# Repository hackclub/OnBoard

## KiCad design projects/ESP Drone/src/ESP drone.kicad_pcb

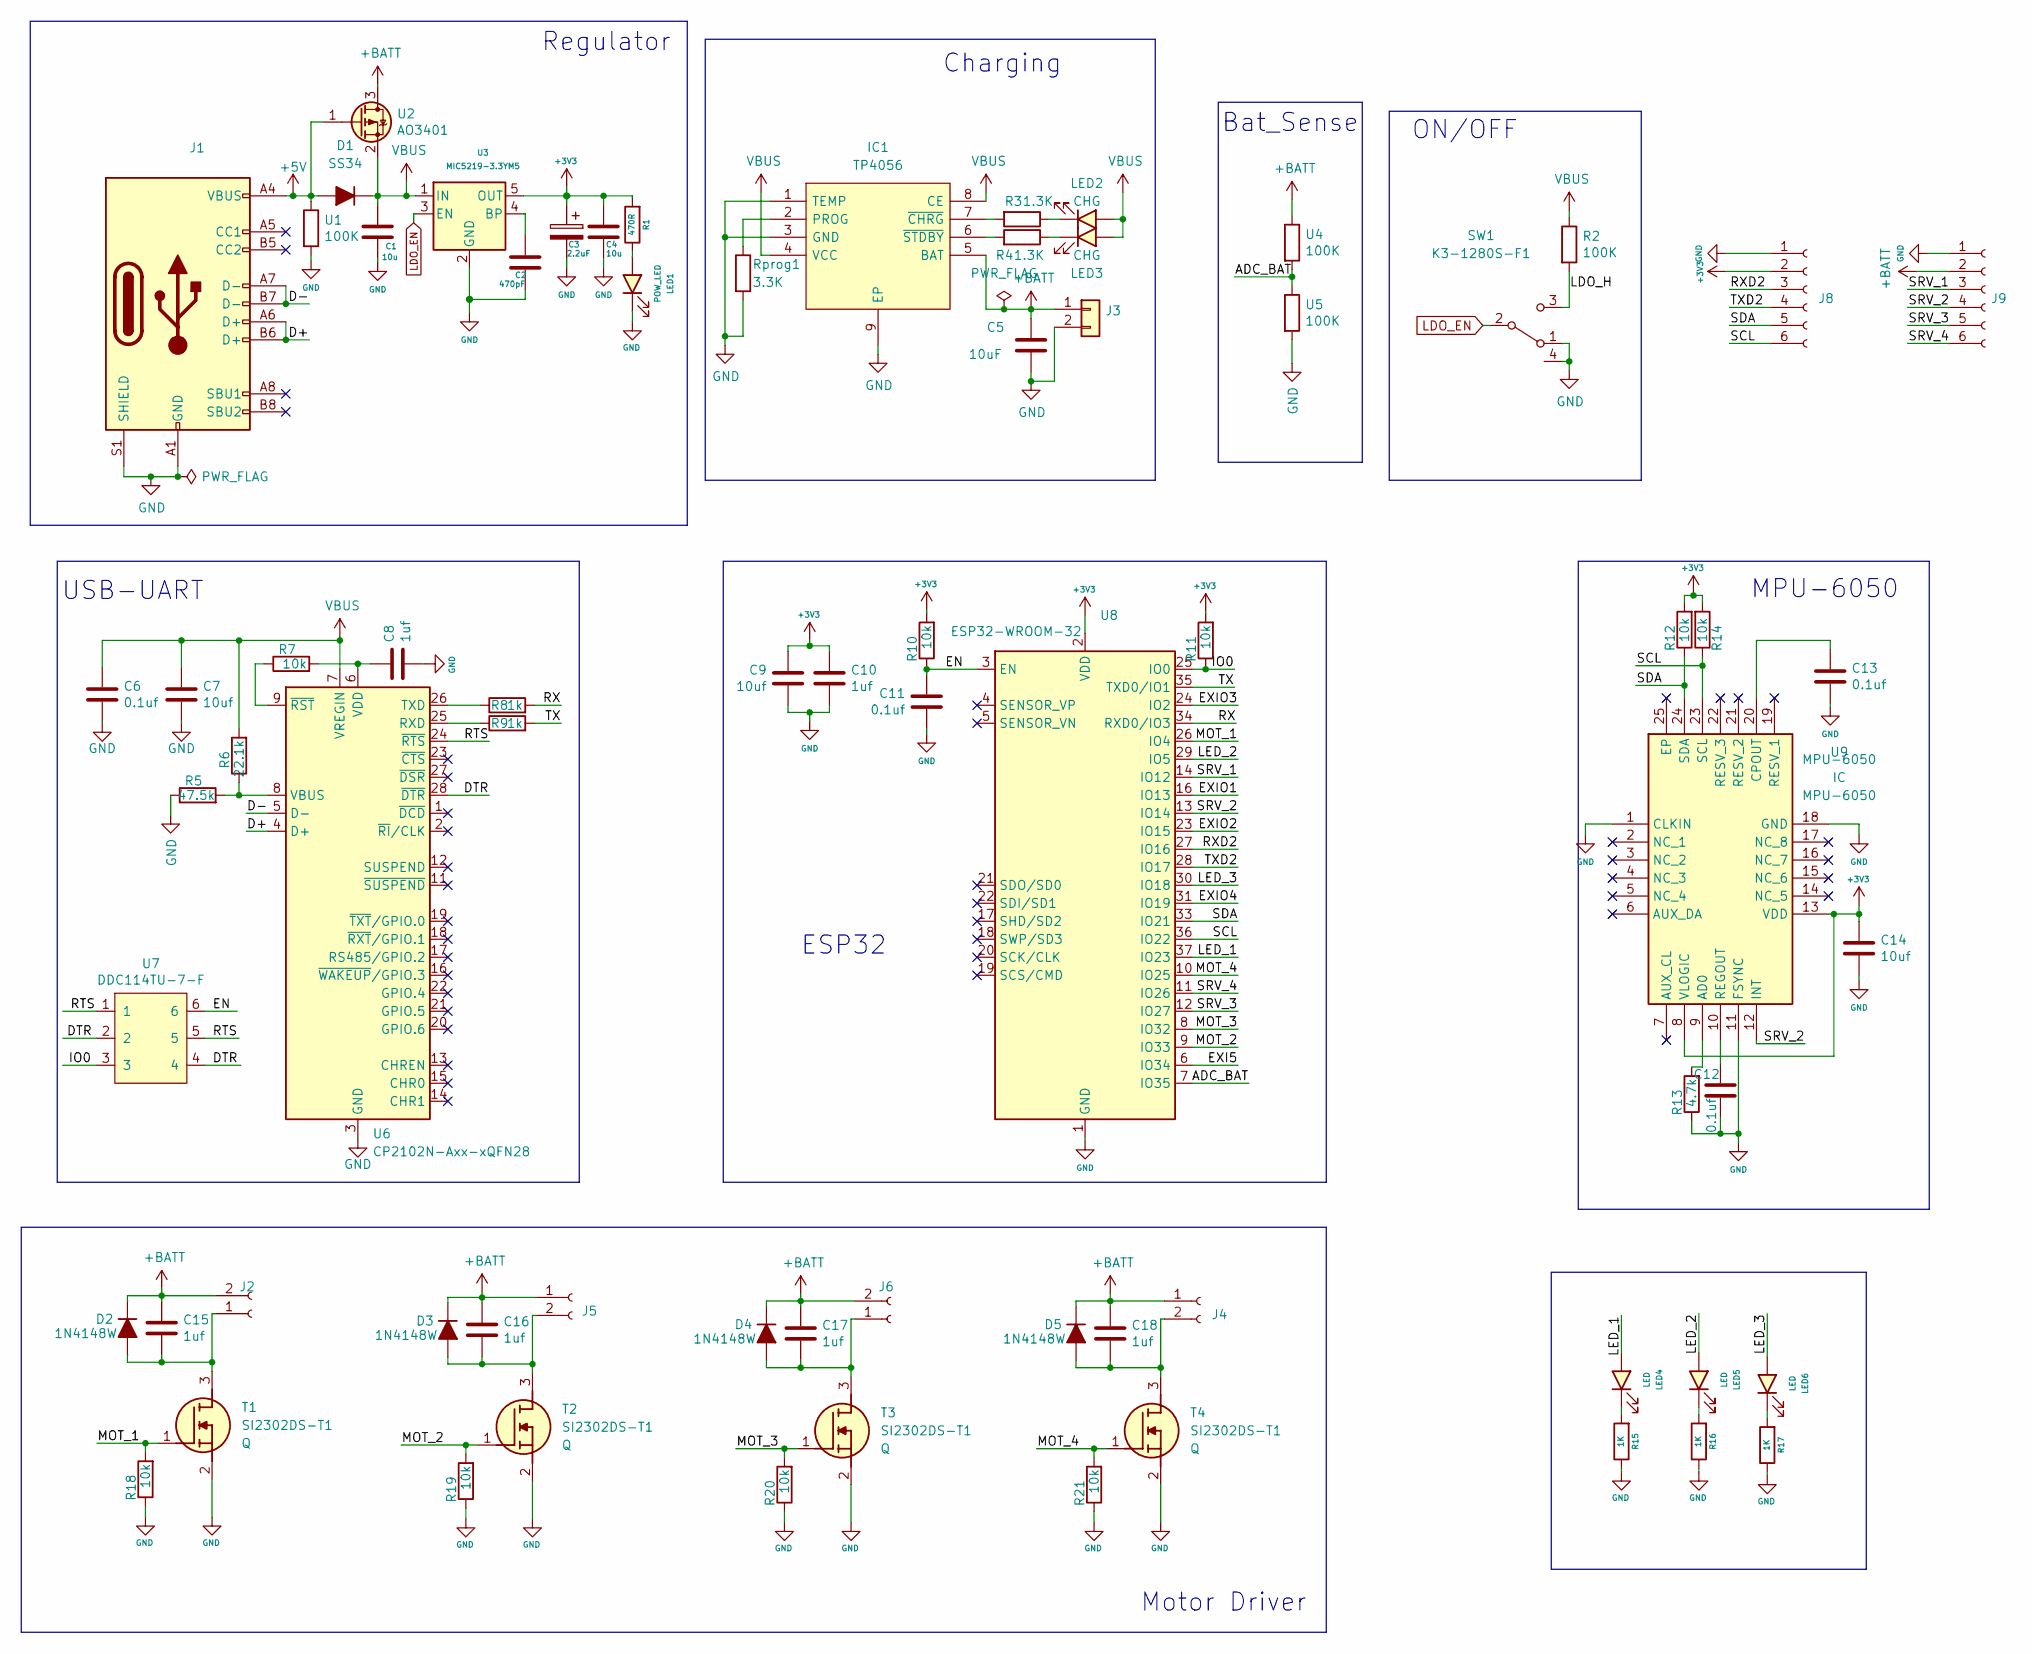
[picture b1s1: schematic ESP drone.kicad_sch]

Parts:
C1, C4: 10u; C_0603_1608Metric
C2: 470pF; C_0603_1608Metric
C3: 2.2uF; C_0805_2012Metric
C5: 10uF; C_0603_1608Metric
C6, C11, C12, C13: 0.1uf; C_0603_1608Metric
C7, C9, C14: 10uf; C_0603_1608Metric
C8, C10, C15, C16, C17, C18: 1uf; C_0603_1608Metric
D1: SS34; D_SMA
D2, D3, D4, D5: 1N4148W; D_SOD-323
IC1: TP4056; SOIC127P600X175-9N; Manufacturer_Part_Number TP4056-42-ESOP8
J1: USB_C_Receptacle_USB2.0; USB_C_Receptacle_HRO_TYPE-C-31-M-12
J2, J4, J5, J6: Conn_01x02_Female; JST_GH_SM02B-GHS-TB_1x02-1MP_P1.25mm_Horizontal
J3: B2B-PH-SM4-TB(LF)(SN); JST_PH_B2B-PH-SM4-TB_1x02-1MP_P2.00mm_Vertical
J8, J9: Conn_01x06_Female; PinHeader_1x06_P2.54mm_Vertical
LED1: POW_LED; LED_0603_1608Metric
LED2, LED3: CHG; LED_0603_1608Metric
LED4, LED5, LED6: LED; LED_0603_1608Metric
R1: 470R; R_0603_1608Metric
R2: 100K; R_0603_1608Metric
R3, R4: 1.3K; R_0603_1608Metric
R5: 47.5k; R_0603_1608Metric
R6: 22.1k; R_0603_1608Metric
R7, R10, R11, R12, R14, R18, R19, R20, R21: 10k; R_0603_1608Metric
R8, R9: 1k; R_0603_1608Metric
R13: 4.7k; R_0603_1608Metric
R15, R16, R17: 1K; R_0603_1608Metric
Rprog1: 3.3K; R_0603_1608Metric
SW1: K3-1280S-F1; slide switch spdt
T1, T2, T3, T4: SI2302DS-T1; SOT95P237X112-3N; Mouser Part Number 781-SI2302DS
U1, U4, U5: 100K; R_0603_1608Metric
U2: AO3401; SOT-23
U3: MIC5219-3.3YM5; SOT-23-5
U6: CP2102N-Axx-xQFN28; QFN-28-1EP_5x5mm_P0.5mm_EP3.35x3.35mm
U7: DDC114TU-7-F; SOT-363_SC-70-6
U8: ESP32-WROOM-32
U9: MPU-6050; MPU6050; Mouser Part Number 410-MPU-6050

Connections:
+3V3: C3.1, C4.1, C9.1, C10.1, C14.1, J8.2, R1.2, R10.2, R11.2, R12.2, R14.2, U3.5 (OUT), U8.2 (VDD), U9.8 (VLOGIC), U9.13 (VDD)
+5V: D1.2 (A), J1.A4 (VBUS), J1.A9 (VBUS), J1.B4 (VBUS), J1.B9 (VBUS), U1.1, U2.1 (G)
+BATT: C5.1, C15.1, C16.1, C17.1, C18.1, D2.1 (K), D3.1 (K), D4.1 (K), D5.1 (K), IC1.5 (BAT), J2.2, J3.1, J4.1, J5.1, J6.2, J9.2, U2.3 (D), U4.1
/ADC_BAT: U4.2, U5.1, U8.7 (IO35)
/D+: J1.A6 (D+), J1.B6 (D+), U6.4 (D+)
/D-: J1.A7 (D-), J1.B7 (D-), U6.5 (D-)
/DTR: U6.28 (~DTR), U7.2, U7.4
/EN: C11.1, R10.1, U7.6, U8.3 (EN)
/EXI5: U8.6 (IO34)
/EXIO1: U8.16 (IO13)
/EXIO2: U8.23 (IO15)
/EXIO3: U8.24 (IO2)
/EXIO4: U8.31 (IO19)
/IO0: R11.1, U7.3, U8.25 (IO0)
/LDO_H: R2.2, SW1.3 (C)
/LED_1: LED4.2 (A), U8.37 (IO23)
/LED_2: LED5.2 (A), U8.29 (IO5)
/LED_3: LED6.2 (A), U8.30 (IO18)
/MOT_1: R18.2, T1.1 (G), U8.26 (IO4)
/MOT_2: R19.2, T2.1 (G), U8.9 (IO33)
/MOT_3: R20.2, T3.1 (G), U8.8 (IO32)
/MOT_4: R21.2, T4.1 (G), U8.10 (IO25)
/RTS: U6.24 (~RTS), U7.1, U7.5
/RX: R8.2, U8.34 (RXD0/IO3)
/RXD2: J8.3, U8.27 (IO16)
/SCL: J8.6, R14.1, U8.36 (IO22), U9.23 (SCL)
/SDA: J8.5, R12.1, U8.33 (IO21), U9.24 (SDA)
/SRV_1: J9.3, U8.14 (IO12)
/SRV_2: J9.4, U8.13 (IO14), U9.12 (INT)
/SRV_3: J9.5, U8.12 (IO27)
/SRV_4: J9.6, U8.11 (IO26)
/TX: R9.2, U8.35 (TXD0/IO1)
/TXD2: J8.4, U8.28 (IO17)
GND: C1.2, C2.2, C3.2, C4.2, C5.2, C6.2, C7.2, C8.2, C9.2, C10.2, C11.2, C12.2, C13.2, C14.2, IC1.1 (TEMP), IC1.3 (GND), IC1.9 (EP), J1.A1 (GND), J1.A12 (GND), J1.B1 (GND), J1.B12 (GND), J1.S1 (SHIELD), J3.2, J8.1, J9.1, LED1.1 (K), R5.1, R13.1, R15.1, R16.1, R17.1, R18.1, R19.1, R20.1, R21.1, Rprog1.2, SW1.1 (A), SW1.4, T1.2 (S), T2.2 (S), T3.2 (S), T4.2 (S), U1.2, U3.2 (GND), U5.2, U6.3 (GND), U6.29 (GND), U8.1 (GND), U8.15 (GND), U8.38 (GND), U8.39 (GND), U9.1 (CLKIN), U9.11 (FSYNC), U9.18 (GND)
LDO_EN: SW1.2 (B), U3.3 (EN)
unnamed: C15.2, D2.2 (A), J2.1, T1.3 (D)
unnamed: C16.2, D3.2 (A), J5.2, T2.3 (D)
unnamed: C17.2, D4.2 (A), J6.1, T3.3 (D)
unnamed: C18.2, D5.2 (A), J4.2, T4.3 (D)
unnamed: IC1.2 (PROG), Rprog1.1
unnamed: IC1.7 (~CHRG), R3.2
unnamed: IC1.6 (~STDBY), R4.2
unnamed: LED1.2 (A), R1.1
unnamed: LED2.1 (K), R3.1
unnamed: LED3.1 (K), R4.1
unnamed: LED4.1 (K), R15.2
unnamed: LED5.1 (K), R16.2
unnamed: LED6.1 (K), R17.2
unnamed: C2.1, U3.4 (BP)
unnamed: R9.1, U6.25 (RXD)
unnamed: R8.1, U6.26 (TXD)
unnamed: R5.2, R6.1, U6.8 (VBUS)
unnamed: C8.1, R7.2, U6.6 (VDD)
unnamed: R7.1, U6.9 (~RST)
unnamed: R13.2, U9.9 (AD0)
unnamed: C13.1, U9.20 (CPOUT)
unnamed: C12.1, U9.10 (REGOUT)
VBUS: C1.1, C6.1, C7.1, D1.1 (K), IC1.4 (VCC), IC1.8 (CE), LED2.2 (A), LED3.2 (A), R2.1, R6.2, U2.2 (S), U3.1 (IN), U6.7 (VREGIN)

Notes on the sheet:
ESP32
ON/OFF
Bat_Sense
Motor Driver
Charging
MPU-6050
Regulator
USB-UART

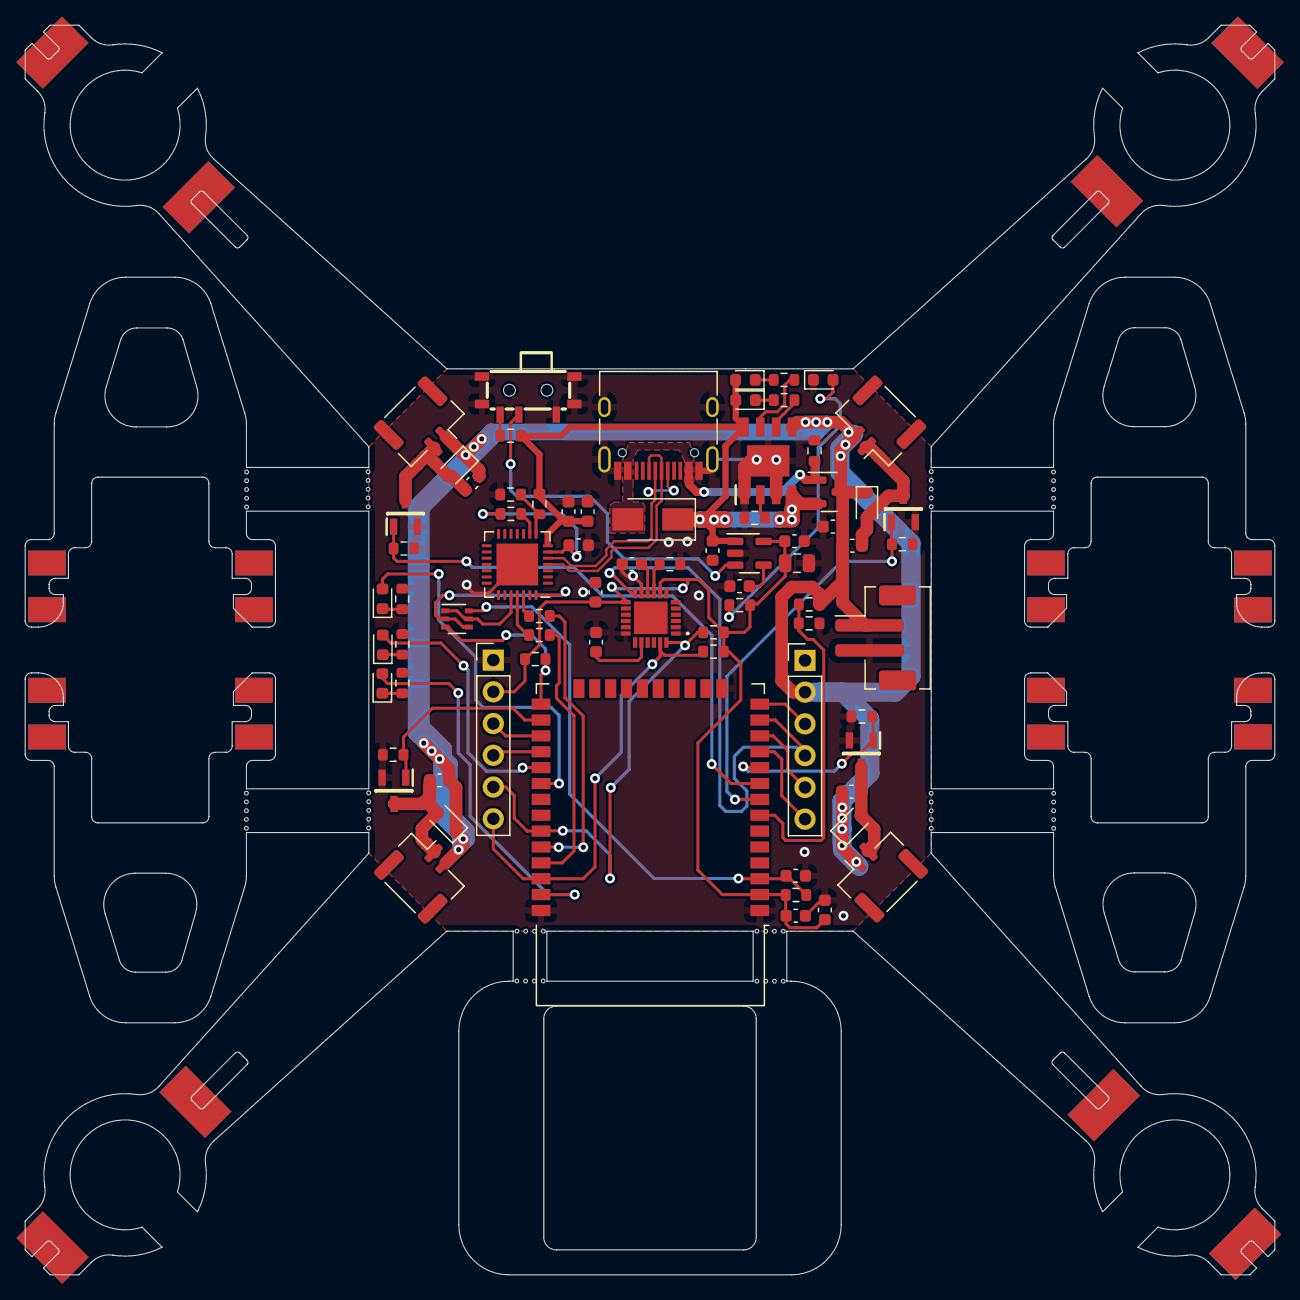
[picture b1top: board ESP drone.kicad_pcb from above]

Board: 2 copper layers, 100.0 x 100.0 mm, 74 parts (0 on the bottom side), 53 nets.

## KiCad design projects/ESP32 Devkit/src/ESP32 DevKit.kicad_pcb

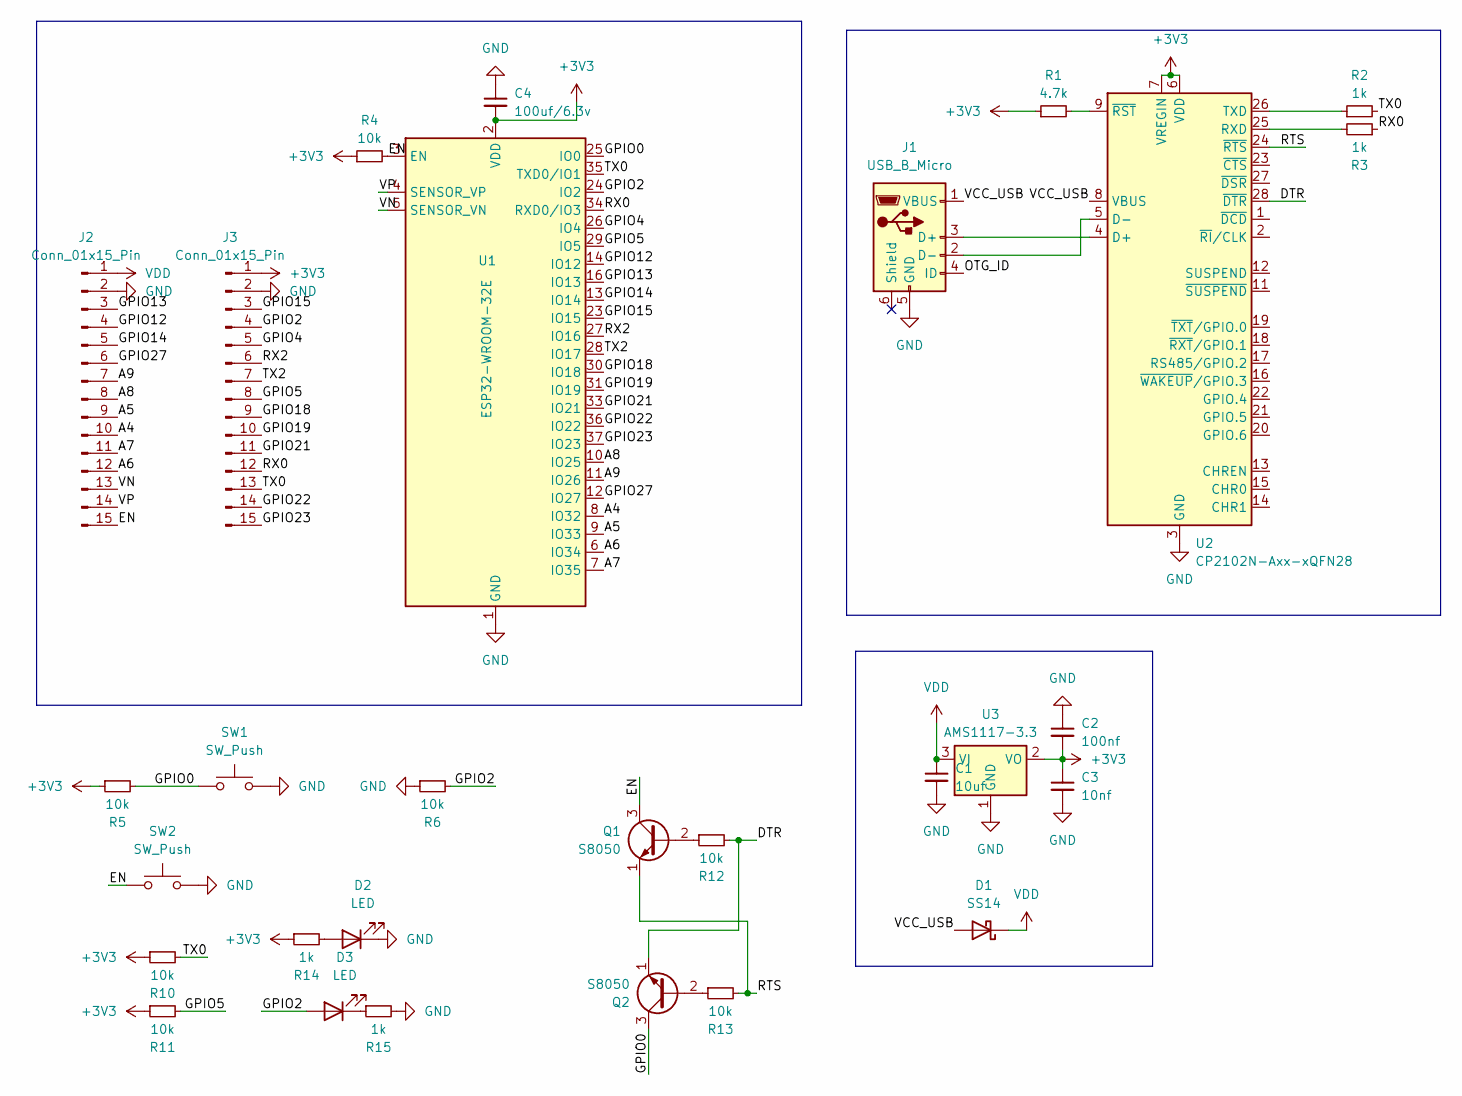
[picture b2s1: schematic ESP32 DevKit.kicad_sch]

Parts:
C1: 10uf; C_0603_1608Metric
C2: 100nf; C_0603_1608Metric
C3: 10nf; C_0603_1608Metric
C4: 100uf/6.3v; C_1206_3216Metric_Pad1.33x1.80mm_HandSolder
D1: SS14; D_SOD-123
D2, D3: LED; LED_0805_2012Metric_Pad1.15x1.40mm_HandSolder
J1: USB_B_Micro; USB_Micro-B_Amphenol_10118194-0001LF_Horizontal
J2, J3: Conn_01x15_Pin; PinHeader_1x15_P2.54mm_Vertical
Q1, Q2: S8050; TSOT-23
R1: 4.7k; R_0603_1608Metric_Pad0.98x0.95mm_HandSolder
R2, R3, R14, R15: 1k; R_0603_1608Metric_Pad0.98x0.95mm_HandSolder
R4, R5, R6, R10, R11, R12, R13: 10k; R_0603_1608Metric_Pad0.98x0.95mm_HandSolder
SW1, SW2: SW_Push; SW_Push_SPST_NO_Alps_SKRK
U1: ESP32-WROOM-32E; ESP32-WROOM-32D
U2: CP2102N-Axx-xQFN28; QFN-28-1EP_5x5mm_P0.5mm_EP3.35x3.35mm
U3: AMS1117-3.3; SOT-223-3_TabPin2

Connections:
+3V3: C2.2, C3.1, C4.2, J3.1, R1.1, R4.1, R5.1, R10.1, R11.1, R14.1, U1.2 (VDD), U2.6 (VDD), U2.7 (VREGIN), U3.2 (VO)
/A4: J2.10, U1.8 (IO32)
/A5: J2.9, U1.9 (IO33)
/A6: J2.12, U1.6 (IO34)
/A7: J2.11, U1.7 (IO35)
/A8: J2.8, U1.10 (IO25)
/A9: J2.7, U1.11 (IO26)
/DTR: Q2.1 (E), R12.2, U2.28 (~DTR)
/EN: J2.15, Q1.3 (C), R4.2, SW2.1, U1.3 (EN)
/GPIO0: Q2.3 (C), R5.2, SW1.1, U1.25 (IO0)
/GPIO2: D3.2 (A), J3.4, R6.2, U1.24 (IO2)
/GPIO4: J3.5, U1.26 (IO4)
/GPIO5: J3.8, R11.2, U1.29 (IO5)
/GPIO12: J2.4, U1.14 (IO12)
/GPIO13: J2.3, U1.16 (IO13)
/GPIO14: J2.5, U1.13 (IO14)
/GPIO15: J3.3, U1.23 (IO15)
/GPIO18: J3.9, U1.30 (IO18)
/GPIO19: J3.10, U1.31 (IO19)
/GPIO21: J3.11, U1.33 (IO21)
/GPIO22: J3.14, U1.36 (IO22)
/GPIO23: J3.15, U1.37 (IO23)
/GPIO27: J2.6, U1.12 (IO27)
/RTS: Q1.1 (E), R13.2, U2.24 (~RTS)
/RX0: J3.12, R3.1, U1.34 (RXD0/IO3)
/RX2: J3.6, U1.27 (IO16)
/TX0: J3.13, R2.2, R10.2, U1.35 (TXD0/IO1)
/TX2: J3.7, U1.28 (IO17)
/VCC_USB: D1.2 (A), J1.1 (VBUS), U2.8 (VBUS); also elsewhere on the board
/VN: J2.13, U1.5 (SENSOR_VN)
/VP: J2.14, U1.4 (SENSOR_VP)
GND: C1.2, C2.1, C3.2, C4.1, D2.1 (K), J1.5 (GND), J2.2, J3.2, R6.1, R15.2, SW1.2, SW2.2, U1.1 (GND), U1.15 (GND), U1.38 (GND), U1.39 (GND), U2.3 (GND), U2.29 (GND), U3.1 (GND); also elsewhere on the board
unnamed: D2.2 (A), R14.2
unnamed: D3.1 (K), R15.1
unnamed 34: J1.3 (D+), U2.4 (D+); also elsewhere on the board
unnamed 35: J1.2 (D-), U2.5 (D-); also elsewhere on the board
unnamed: Q1.2 (B), R12.1
unnamed: Q2.2 (B), R13.1
unnamed: R3.2, U2.25 (RXD)
unnamed: R2.1, U2.26 (TXD)
unnamed: R1.2, U2.9 (~RST)
VDD: C1.1, D1.1 (K), J2.1, U3.3 (VI)

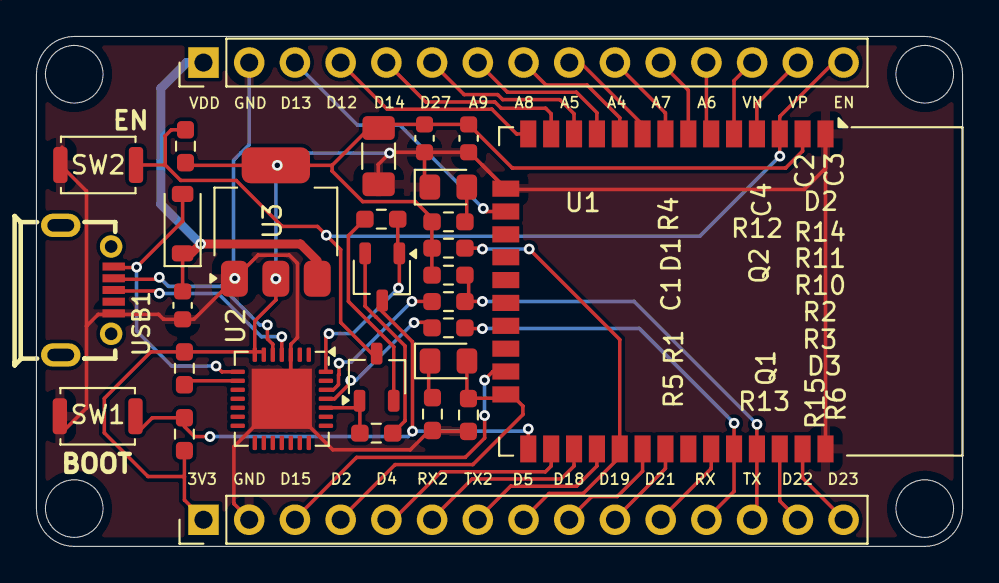
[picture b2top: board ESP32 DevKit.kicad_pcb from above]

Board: 2 copper layers, 51.5 x 28.3 mm, 29 parts (0 on the bottom side), 42 nets.

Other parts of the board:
USB1: MICRO-USB-SMD_MICRO-USB-18

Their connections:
/VCC_USB: USB1.1; also elsewhere on the board
GND: USB1.5; also elsewhere on the board
unnamed 34: USB1.3; also elsewhere on the board
unnamed 35: USB1.2; also elsewhere on the board

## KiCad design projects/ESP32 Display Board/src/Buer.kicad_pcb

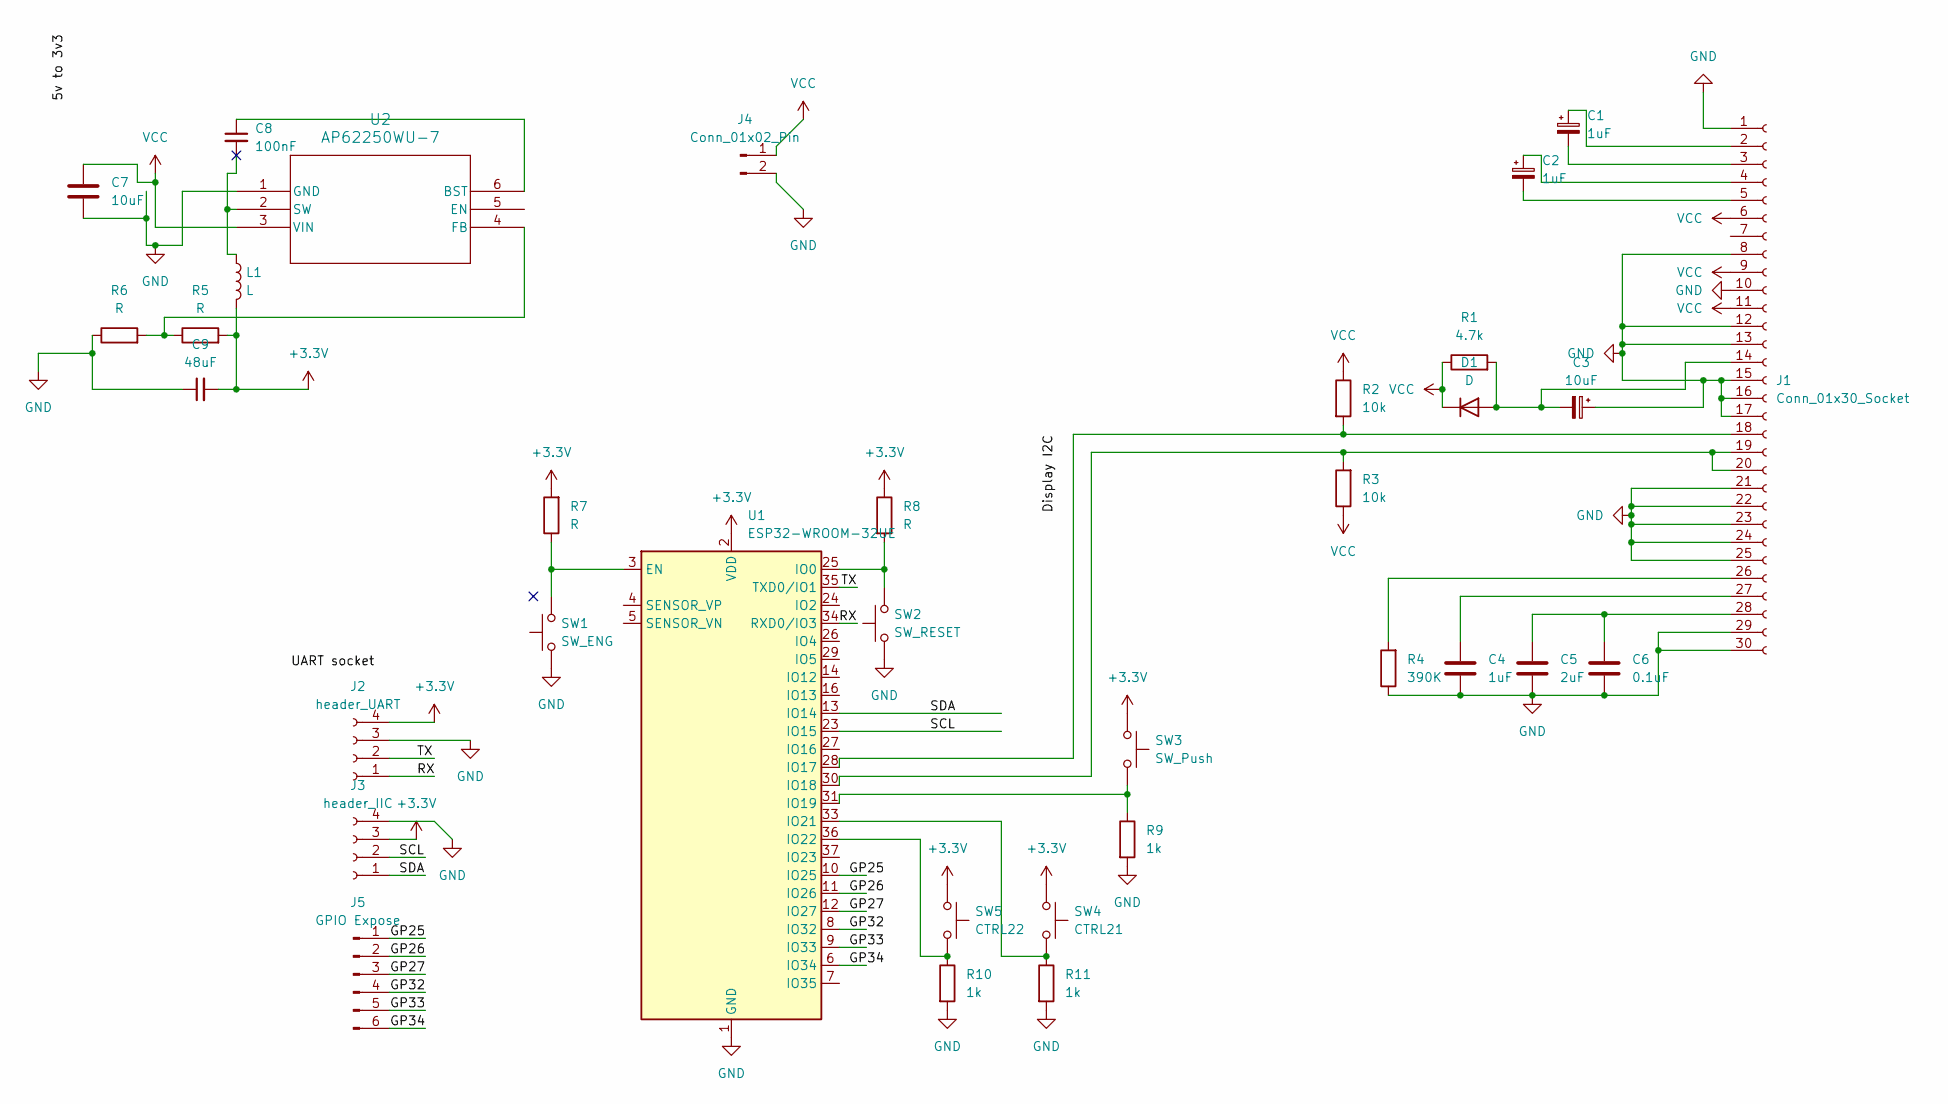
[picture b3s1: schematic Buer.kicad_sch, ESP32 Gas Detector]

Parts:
C1, C2, C4: 1uF; C_1812_4532Metric
C3, C7: 10uF; C_1812_4532Metric
C5: 2uF; C_1812_4532Metric
C6: 0.1uF; C_1206_3216Metric
C8: 100nF; C_1812_4532Metric
C9: 48uF; C_1812_4532Metric
D1: D; D_1206_3216Metric
J1: Conn_01x30_Socket; Hirose_FH12-30S-0.5SH_1x30-1MP_P0.50mm_Horizontal
J2: header_UART; JST_EH_B4B-EH-A_1x04_P2.50mm_Vertical
J3: header_IIC; NS-Tech_Grove_1x04_P2mm_Vertical
J4: Conn_01x02_Pin; TestPoint_2Pads_Pitch5.08mm_Drill1.3mm
J5: GPIO Expose; JST_PH_B6B-PH-K_1x06_P2.00mm_Vertical
L1: L; L_2010_5025Metric
R1: 4.7k; R_2512_6332Metric
R2, R3: 10k; R_2512_6332Metric
R4: 390K; R_2512_6332Metric
R5, R6, R7, R8: R; R_2512_6332Metric
R9, R10, R11: 1k; R_2512_6332Metric
SW1: SW_ENG; SW_Tactile_SPST_NO_Straight_CK_PTS636Sx25SMTRLFS
SW2: SW_RESET; SW_Tactile_SPST_NO_Straight_CK_PTS636Sx25SMTRLFS
SW3: SW_Push; SW_Tactile_SPST_NO_Straight_CK_PTS636Sx25SMTRLFS
SW4: CTRL21; SW_Tactile_SPST_NO_Straight_CK_PTS636Sx25SMTRLFS
SW5: CTRL22; SW_Tactile_SPST_NO_Straight_CK_PTS636Sx25SMTRLFS
U1: ESP32-WROOM-32UE
U2: AP62250WU-7; TSOT-23-6

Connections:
+3.3V: C9.2, J2.4, J3.3, L1.2, R5.2, R7.2, R8.1, SW3.1, SW4.1, SW5.1, U1.2 (VDD)
/GP25: J5.1, U1.10 (IO25); also elsewhere on the board
/GP26: J5.2, U1.11 (IO26); also elsewhere on the board
/GP27: J5.3, U1.12 (IO27); also elsewhere on the board
/GP32: J5.4, U1.8 (IO32); also elsewhere on the board
/GP33: J5.5, U1.9 (IO33); also elsewhere on the board
/GP34: J5.6, U1.6 (IO34); also elsewhere on the board
/RX: J2.1, U1.34 (RXD0/IO3)
/SCL: J3.2, U1.23 (IO15)
/SDA: J3.1, U1.13 (IO14)
/TX: J2.2, U1.35 (TXD0/IO1)
GND: C3.1, C4.2, C5.2, C6.2, C7.2, C9.1, J1.1, J1.8, J1.10, J1.12, J1.13, J1.15, J1.16, J1.17, J1.21, J1.22, J1.23, J1.24, J1.25, J1.29, J1.30, J2.3, J3.4, J4.2, R4.1, R6.1, R9.2, R10.2, R11.2, SW1.1, SW2.1, U1.1 (GND), U1.15 (GND), U1.38 (GND), U1.39 (GND), U2.1 (GND)
unnamed: C3.2, D1.2 (A), J1.14, R1.2
unnamed: C1.1, J1.2
unnamed: C1.2, J1.3
unnamed: C2.1, J1.4
unnamed: C2.2, J1.5
unnamed: J1.18, R2.2, U1.28 (IO17)
unnamed: J1.19, J1.20, R3.2, U1.30 (IO18)
unnamed: J1.26, R4.2
unnamed: C4.1, J1.27
unnamed: C5.1, C6.1, J1.28
unnamed: R7.1, SW1.2, U1.3 (EN)
unnamed: R8.2, SW2.2, U1.25 (IO0)
unnamed: R9.1, SW3.2, U1.31 (IO19)
unnamed: R11.1, SW4.2, U1.33 (IO21)
unnamed: R10.1, SW5.2, U1.36 (IO22)
unnamed: C8.1, U2.6 (BST)
unnamed: R5.1, R6.2, U2.4 (FB)
VCC: C7.1, D1.1 (K), J1.6, J1.9, J1.11, J4.1, R1.1, R2.1, R3.1, U2.3 (VIN)

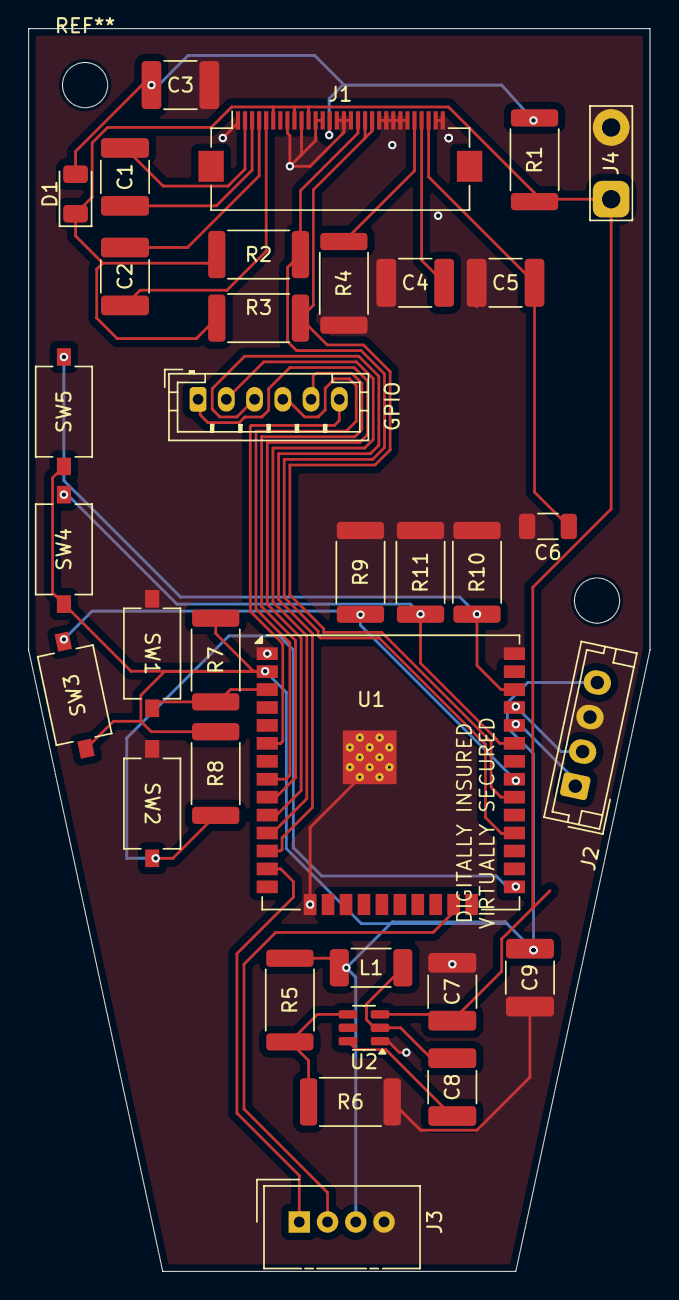
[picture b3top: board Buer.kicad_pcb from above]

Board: 2 copper layers, 44.0 x 88.0 mm, 34 parts (0 on the bottom side), 30 nets.

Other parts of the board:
GPIO: GPIO Expose; JST_PH_B6B-PH-K_1x06_P2.00mm_Vertical

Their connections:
/GP25: GPIO.1; also elsewhere on the board
/GP26: GPIO.2; also elsewhere on the board
/GP27: GPIO.3; also elsewhere on the board
/GP32: GPIO.4; also elsewhere on the board
/GP33: GPIO.5; also elsewhere on the board
/GP34: GPIO.6; also elsewhere on the board

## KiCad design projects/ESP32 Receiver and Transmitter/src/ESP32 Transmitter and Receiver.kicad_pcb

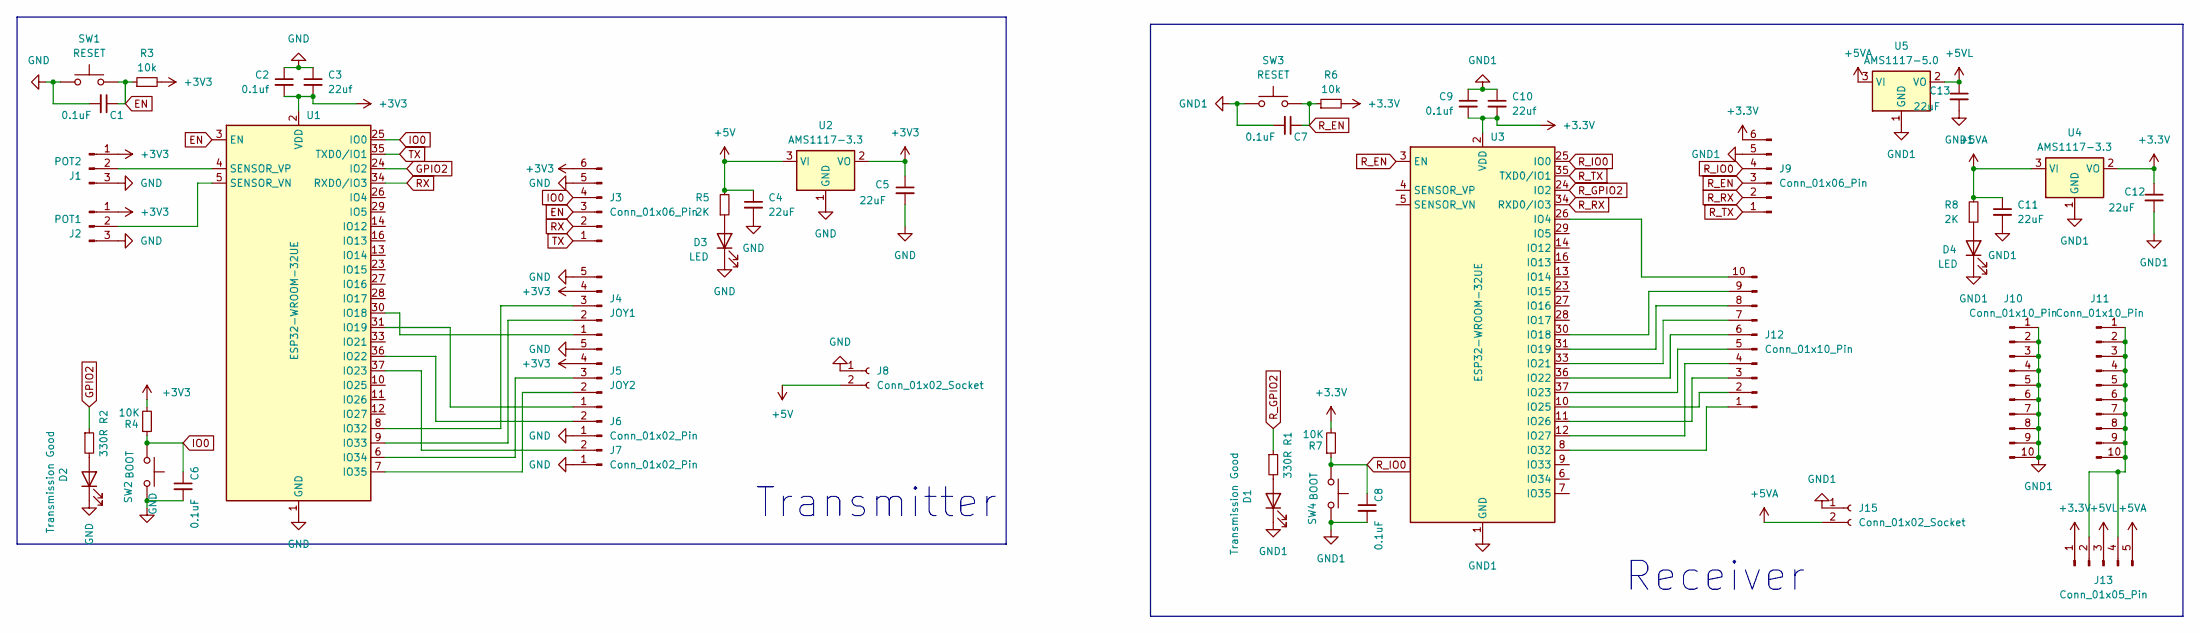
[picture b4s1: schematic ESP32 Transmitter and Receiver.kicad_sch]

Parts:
C1, C6, C7: 0.1uF; C_0805_2012Metric_Pad1.18x1.45mm_HandSolder
C2, C9: 0.1uf; C_0805_2012Metric_Pad1.18x1.45mm_HandSolder
C3, C10: 22uf; C_0805_2012Metric_Pad1.18x1.45mm_HandSolder
C4, C5, C11, C12, C13: 22uF; C_0805_2012Metric_Pad1.18x1.45mm_HandSolder
C8: 0.1uF; C_1206_3216Metric_Pad1.33x1.80mm_HandSolder
D1, D2: Transmission Good; LED_0805_2012Metric_Pad1.15x1.40mm_HandSolder
D3, D4: LED; LED_0805_2012Metric_Pad1.15x1.40mm_HandSolder
J1: POT2; PinHeader_1x03_P2.54mm_Vertical
J2: POT1; PinHeader_1x03_P2.54mm_Vertical
J3, J9: Conn_01x06_Pin; PinHeader_1x06_P2.54mm_Vertical
J4: JOY1; PinHeader_1x05_P2.54mm_Vertical
J5: JOY2; PinHeader_1x05_P2.54mm_Vertical
J6, J7: Conn_01x02_Pin; PinHeader_1x02_P2.54mm_Vertical
J8, J15: Conn_01x02_Socket; PinHeader_1x02_P2.54mm_Vertical
J10, J11, J12: Conn_01x10_Pin; PinHeader_1x10_P2.54mm_Vertical
J13: Conn_01x05_Pin; PinSocket_1x05_P2.54mm_Vertical
R1, R2: 330R; R_0805_2012Metric_Pad1.20x1.40mm_HandSolder
R3, R6: 10k; R_0805_2012Metric_Pad1.20x1.40mm_HandSolder
R4, R7: 10K; R_0805_2012Metric_Pad1.20x1.40mm_HandSolder
R5: 2K; R_0805_2012Metric_Pad1.20x1.40mm_HandSolder
R8: 2K; R_1206_3216Metric_Pad1.30x1.75mm_HandSolder
SW1, SW3: RESET; SW_Push_SPST_NO_Alps_SKRK
SW2, SW4: BOOT; SW_Push_SPST_NO_Alps_SKRK
U1, U3: ESP32-WROOM-32UE; ESP32-WROOM-32E
U2, U4: AMS1117-3.3; SOT-223-3_TabPin2
U5: AMS1117-5.0; SOT-223-3_TabPin2

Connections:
+3.3V: C9.2, C10.2, C12.1, J9.6, J13.1, R6.2, R7.2, U3.2 (VDD), U4.2 (VO)
+3V3: C2.2, C3.2, C5.1, J1.1, J2.1, J3.6, J4.4, J5.4, R3.2, R4.2, U1.2 (VDD), U2.2 (VO)
+5V: C4.1, J8.2, R5.2, U2.3 (VI)
+5VA: C11.1, J13.5, J15.2, R8.2, U4.3 (VI), U5.3 (VI)
+5VL: C13.1, J13.3, U5.2 (VO)
EN: C1.1, J3.3, R3.1, SW1.2, U1.3 (EN)
GND: C1.2, C2.1, C3.1, C4.2, C5.2, C6.2, D2.1 (K), D3.1 (K), J1.3, J2.3, J3.5, J4.5, J5.5, J6.1, J7.1, J8.1, SW1.1, SW2.2, U1.1 (GND), U1.15 (GND), U1.38 (GND), U1.39 (GND), U2.1 (GND)
GND1: C7.2, C8.2, C9.1, C10.1, C11.2, C12.2, C13.2, D1.1 (K), D4.1 (K), J9.5, J10.1, J10.2, J10.3, J10.4, J10.5, J10.6, J10.7, J10.8, J10.9, J10.10, J15.1, SW3.1, SW4.2, U3.1 (GND), U3.15 (GND), U3.38 (GND), U3.39 (GND), U4.1 (GND), U5.1 (GND)
GPIO2: R2.1, U1.24 (IO2)
IO0: C6.1, J3.4, R4.1, SW2.1, U1.25 (IO0)
unnamed: D1.2 (A), R1.2
unnamed: D2.2 (A), R2.2
unnamed: D3.2 (A), R5.1
unnamed: D4.2 (A), R8.1
unnamed: J1.2, U1.4 (SENSOR_VP)
unnamed: J2.2, U1.5 (SENSOR_VN)
unnamed: J4.1, U1.30 (IO18)
unnamed: J4.2, U1.9 (IO33)
unnamed: J4.3, U1.8 (IO32)
unnamed: J5.1, U1.31 (IO19)
unnamed: J5.2, U1.7 (IO35)
unnamed: J5.3, U1.6 (IO34)
unnamed: J6.2, U1.36 (IO22)
unnamed: J7.2, U1.37 (IO23)
unnamed: J11.1, J11.2, J11.3, J11.4, J11.5, J11.6, J11.7, J11.8, J11.9, J11.10, J13.2, J13.4
unnamed: J12.1, U3.8 (IO32)
unnamed: J12.2, U3.10 (IO25)
unnamed: J12.3, U3.11 (IO26)
unnamed: J12.4, U3.12 (IO27)
unnamed: J12.5, U3.37 (IO23)
unnamed: J12.6, U3.36 (IO22)
unnamed: J12.7, U3.33 (IO21)
unnamed: J12.8, U3.31 (IO19)
unnamed: J12.9, U3.30 (IO18)
unnamed: J12.10, U3.26 (IO4)
RX: J3.2, U1.34 (RXD0/IO3)
R_EN: C7.1, J9.3, R6.1, SW3.2, U3.3 (EN)
R_GPIO2: R1.1, U3.24 (IO2)
R_IO0: C8.1, J9.4, R7.1, SW4.1, U3.25 (IO0)
R_RX: J9.2, U3.34 (RXD0/IO3)
R_TX: J9.1, U3.35 (TXD0/IO1)
TX: J3.1, U1.35 (TXD0/IO1)

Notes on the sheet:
Receiver
Transmitter

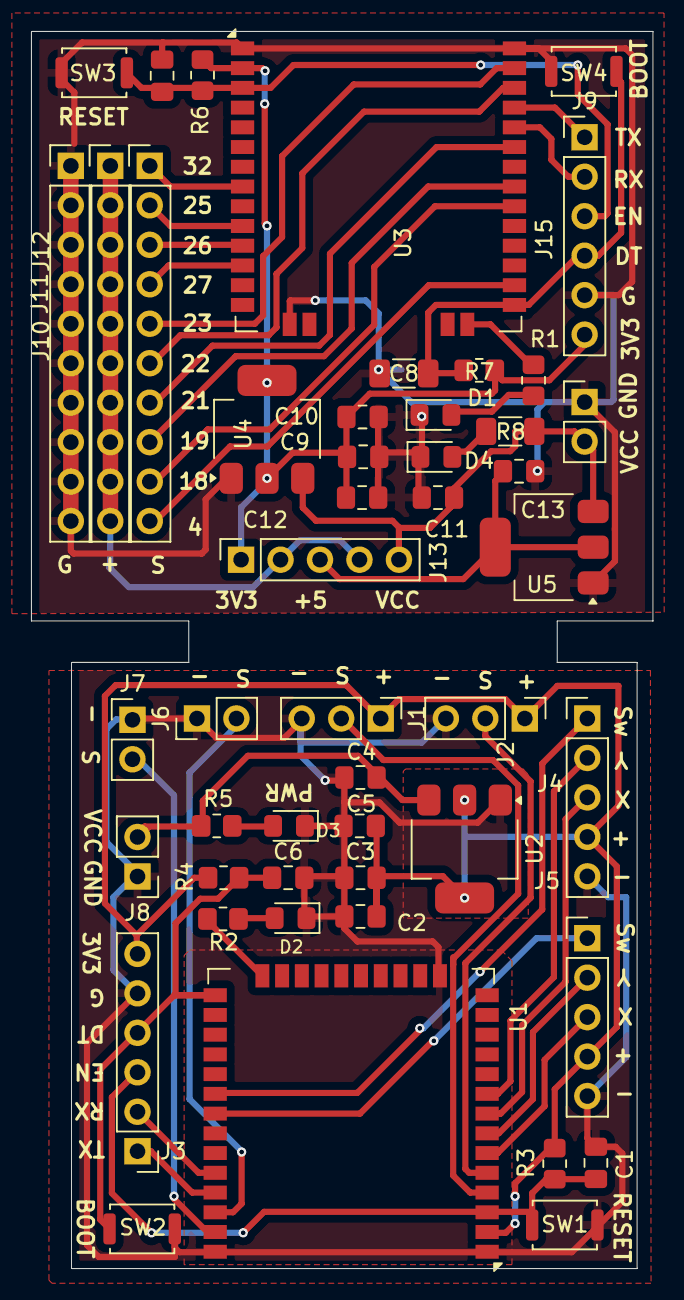
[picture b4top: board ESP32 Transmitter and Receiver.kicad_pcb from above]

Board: 2 copper layers, 40.0 x 79.6 mm, 48 parts (0 on the bottom side), 42 nets.
